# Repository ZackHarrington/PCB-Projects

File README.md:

# PCB Projects
This repository holds all my personal Autodesk Eagle (now Fusion 360 and KiCAD) projects and libraries

__Projects:__
- Billy Bass Board: 	A board to convert or 'hack' a Big Mouth Billy Bass into an IoT device - in progress
- Christmas Snow Globe:	A board using an ATtiny85 as a 6-hour timer IC in a custom snow globe - made as a gift
- Greek Keyboard:	A 5x6 key keyboard using an ATmega32u4 and HID to input Greek Unicode - made as a gift
- LED Test Board:	A simple board for testing any combination of LED, resistor, and power source
- USB UART Board:	Two small boards for programming ESP32 modules, each for a different USB-to-UART IC

__Libraries:__
- Aesthetics:	Silkscreen and copper designs
- Capacitors: 	SEM (Samsung Electro-Mechanics) MLCC capacitors
- Connectors: 	Board inputs or outputs
- Diodes:	Standard and Schottky diodes with Kingbright LEDs
- Energy:	Batteries and energy storage
- ICs: 		Integrates circuits
- Inductors:	SEM (Samsung Electro-Mechanics) Power Inductors
- Oscillators:	Crystal Oscillators
- Resistors:	SEM (Samsung Electro-Mechanics) CHIP-R chip resistors and potentiometers
- Switches: 	Physical buttons and switches
- Symbols:	Schematic symbols
- Transistors:	Discrete MOSFETs and BJTs

__Design Blocks:__
- ESP32 Wrover Module:	All standard capacitors and connections for implementing an ESP32-WROVER module

Note: I'm still in the process of finalizing the documentation for each project

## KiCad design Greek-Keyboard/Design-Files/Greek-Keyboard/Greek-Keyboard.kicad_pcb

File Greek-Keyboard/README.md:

# Greek Keyboard 

This project was built as a request from my brother. His desire was to have a separate keyboard he could use to input Greek letters while writing papers for school. This README goes through an overview of the features, build, and considerations for next time.

## Features

The following were the requested features for this project:
- A separate USB-C keyboard, with a similar look and feel to the Dell XPS-15 (his current laptop)
- Contain all the Greek letters in a small form factor
- If there is extra room add some other common characters (degree symbol, etc.)
- Make it not require Windows language switching

## Design

To meet all these requirements I first came up with a concept for a 5x6 key keyboard, which fit all the Greek letters on the first 4 rows. This left a 5th required row to fit the SHIFT key, and left room for some extra characters. For the extra characters we decided to add the degree symbol along with final sigma, and then add the most common Greek letter accents. For the keyboard keys I decided to go with Cherry MX keys since they were the most readily available and easy to use. The electronics for a keyboard is also relatively straightforward and well documented online. Thus, after some brief research I settled on a 5x6 key matrix to save pin space.  

For the keyboard firmware, and actually sending Windows a Greek character without language switching, I chose to use Unicode inputs. Unicode gives a unique code to every character in the majority of languages. To input a Unicode character you simply have to type in its hexadecimal sequence, followed by ALT + x. This indicates to Windows that the previous input is the hex code for a Unicode character and that they should be converted accordingly. To do this, I internally check for what combination of keys is pressed and then send the corresponding sequence and ALT + x in quick succession. I chose to implement all this through an Arduino Leonardo (ATmega32u4), so I only needed one USB connection for everything.

## Construction

Included below are some images of the final product.

### PCB

### Keyboard Backlights

## License

This is just a hobby creation I made as a gift so feel free to do whatever you want with this design if you happened upon it. However, I would recommend reading the considerations below and modifying it or building your own rather than copying it.

## Project Considerations

The following are some things I learned from this project for myself or anyone else to consider when doing something similar.
- Add an ICSP header and !RESET pin pullup - The ATmega32u4 does not come with a USB bootloader and you first have to program it in. This can be done in many different ways, but I chose to use an Arduino and the built in ArduinoISP.
- It would be easier to solder the Cherry keys in by printing the top of the enclosure first and using it to align them
- The keyboard sounds very different once in the enclosure, consider adding some foam or extra support from the enclosure to minimize the hollow clicking sound.

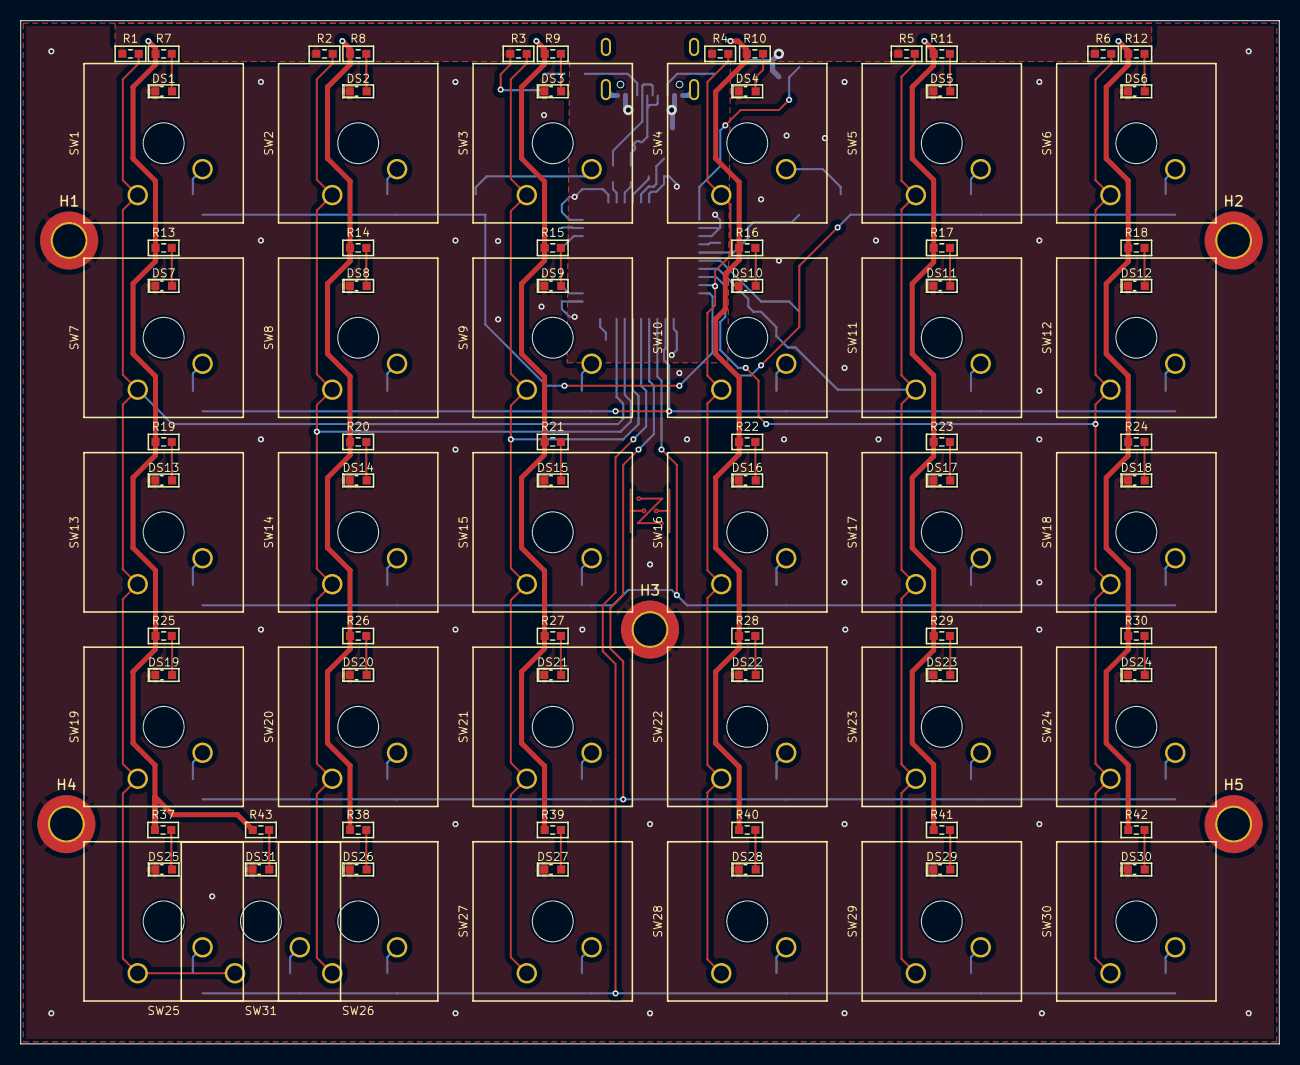
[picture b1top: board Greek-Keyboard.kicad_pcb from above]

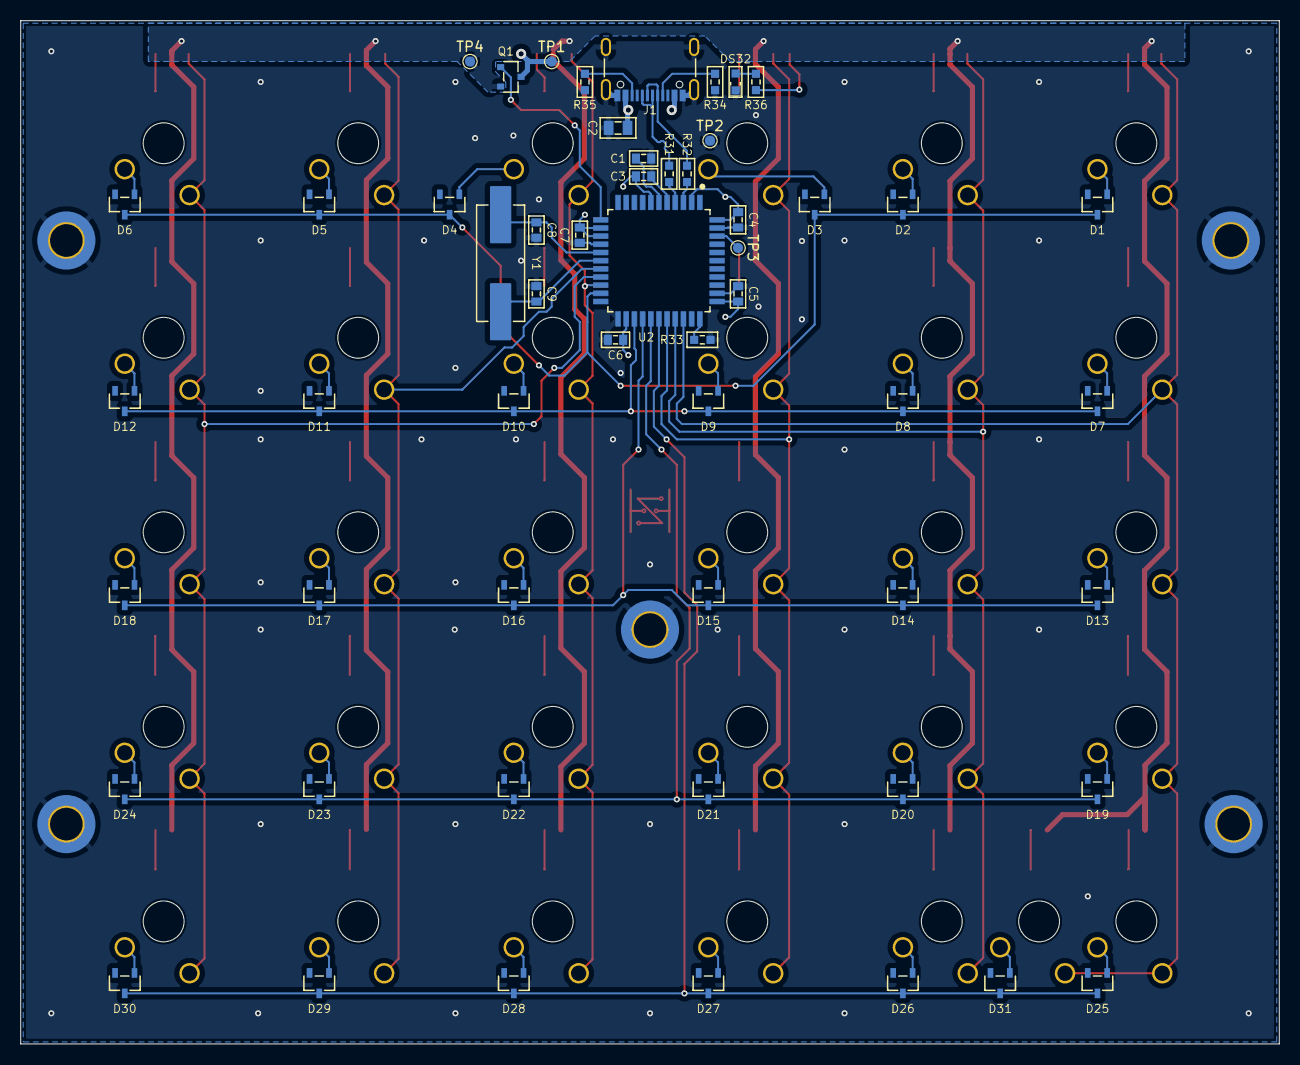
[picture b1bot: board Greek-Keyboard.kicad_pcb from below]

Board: 2 copper layers, 123.2 x 100.2 mm, 160 parts (55 on the bottom side), 89 nets.

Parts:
C1: 1uF±10%; 1608-SEM
C2: 10uF±10%; 2012-SEM
C3, C4, C5, C6, C7: 0.1uF±5%; 1608-SEM
C8, C9: 22pF±5%; 1608-SEM
D1, D2, D3, D4, D5, D6, D7, D8, D9, D10, D11, D12, D13, D14, D15, D16, D17, D18, D19, D20, D21, D22, D23, D24, D25, D26, D27, D28, D29, D30, D31: BAT54L; SOT-23-3
DS1, DS2, DS3, DS4, DS5, DS6, DS7, DS8, DS9, DS10, DS11, DS12, DS13, DS14, DS15, DS16, DS17, DS18, DS19, DS20, DS21, DS22, DS23, DS24, DS25, DS26, DS27, DS28, DS29, DS30, DS31: White; 1608
DS32: RED; 1608
H1, H2, H3, H4, H5: MountingHole_Pad; MountingHole_3.2mm_M3_ISO7380_Pad_TopBottom
J1: USB-C; USB-4105
Q1: BSS316N; SOT-23-3
R1, R2, R3, R4, R5, R6, R7, R8, R9, R10, R11, R12, R13, R14, R15, R16, R17, R18, R19, R20, R21, R22, R23, R24, R25, R26, R27, R28, R29, R30, R36, R37, R38, R39, R40, R41, R42, R43: 470Ω±1%; 1608-SEM
R31, R32: 22Ω±1%; 1608-SEM
R33: 10kΩ±1%; 1608-SEM
R34, R35: 5.1kΩ±1%; 1608-SEM
SW1, SW2, SW3, SW4, SW5, SW6, SW7, SW8, SW9, SW10, SW11, SW12, SW13, SW14, SW15, SW16, SW17, SW18, SW19, SW20, SW21, SW22, SW23, SW24, SW25, SW26, SW27, SW28, SW29, SW30, SW31: MX-Brown; MX-1-Pole
TP1, TP2, TP3, TP4: TestPoint; TestPoint_Pad_D1.0mm
U1: SIGNATURE
U2: ATmega32u4; TQFP44
Y1: 8MHz±25ppm; ABLS-ABRACON

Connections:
+5V: C2.1, C3.1, C4.1, C5.1, C6.1, C7.1, J1.A4_B9 (VBUS), J1.A9_B4 (VBUS), Q1.3, R1.1, R2.1, R3.1, R4.1, R5.1, R6.1, R36.1, TP1.1, U2.2 (UVcc), U2.7 (VBus), U2.13 (!RESET), U2.14 (VCC), U2.24 (AVCC), U2.34 (VCC), U2.44 (AVCC)
/Backlight LEDs/5V: Q1.2, R7.1, R8.1, R9.1, R10.1, R11.1, R12.1, R13.1, R14.1, R15.1, R16.1, R17.1, R18.1, R19.1, R20.1, R21.1, R22.1, R23.1, R24.1, R25.1, R26.1, R27.1, R28.1, R29.1, R30.1, R37.1, R38.1, R39.1, R40.1, R41.1, R42.1, R43.1, TP4.1
/D0: R4.2, SW4.2, SW10.2, SW16.2, SW22.2, SW28.2, U2.20 ((RXD1/INT2)_PD2)
/D1: D1.3, D2.3, D3.3, D4.3, D5.3, D6.3, U2.21 ((TXD1/INT3)_PD3)
/D2: R6.2, SW6.2, SW12.2, SW18.2, SW24.2, SW30.2, U2.19 ((SDA/INT1)_PD1)
/D3: R5.2, SW5.2, SW11.2, SW17.2, SW23.2, SW29.2, U2.18 ((SCL/INT0)_PD0)
/D4: D7.3, D8.3, D9.3, D10.3, D11.3, D12.3, U2.25 ((ICP1/ADC8)_PD4)
/D5: R1.2, SW1.2, SW7.2, SW13.2, SW19.2, SW25.2, SW31.2, U2.31 (PC6)
/D6: D19.3, D20.3, D21.3, D22.3, D23.3, D24.3, U2.27 ((T0/ADC10)_PD7)
/IO8: D25.3, D26.3, D27.3, D28.3, D29.3, D30.3, D31.3, U2.28 ((PCINT4/ADC11)_PB4)
/IO9: R3.2, SW3.2, SW9.2, SW15.2, SW21.2, SW27.2, U2.29 ((PCINT5/ADC12)_PB5)
/IO10: R2.2, SW2.2, SW8.2, SW14.2, SW20.2, SW26.2, U2.30 ((PCINT6/ADC13)_PB6)
/IO11: Q1.1, U2.12 ((PCINT7/!RTS)_PB7)
/IO12: D13.3, D14.3, D15.3, D16.3, D17.3, D18.3, U2.26 ((T1/ADC9)_PD6)
GND: C1.2, C2.2, C3.2, C4.2, C5.2, C6.2, C7.2, C8.1, C9.1, DS1.1, DS2.1, DS3.1, DS4.1, DS5.1, DS6.1, DS7.1, DS8.1, DS9.1, DS10.1, DS11.1, DS12.1, DS13.1, DS14.1, DS15.1, DS16.1, DS17.1, DS18.1, DS19.1, DS20.1, DS21.1, DS22.1, DS23.1, DS24.1, DS25.1, DS26.1, DS27.1, DS28.1, DS29.1, DS30.1, DS31.1, DS32.1, H1.1, H2.1, H3.1, H4.1, H5.1, J1.A1_B12 (GND), J1.A12_B1 (GND), J1.SHELL@1 (SHELL), J1.SHELL@2 (SHELL), J1.SHELL@3 (SHELL), J1.SHELL@4 (SHELL), R33.2, R34.2, R35.2, TP2.1, U2.5 (UGnd), U2.15 (GND), U2.23 (GND), U2.35 (GND), U2.43 (GND)
unnamed: D1.1, SW1.1
unnamed: D2.1, SW2.1
unnamed: D3.1, SW3.1
unnamed: D4.1, SW4.1
unnamed: D5.1, SW5.1
unnamed: D6.1, SW6.1
unnamed: D7.1, SW7.1
unnamed: D8.1, SW8.1
unnamed: D9.1, SW9.1
unnamed: D10.1, SW10.1
unnamed: D11.1, SW11.1
unnamed: D12.1, SW12.1
unnamed: D13.1, SW13.1
unnamed: D14.1, SW14.1
unnamed: D15.1, SW15.1
unnamed: D16.1, SW16.1
unnamed: D17.1, SW17.1
unnamed: D18.1, SW18.1
unnamed: D19.1, SW19.1
unnamed: D20.1, SW20.1
unnamed: D21.1, SW21.1
unnamed: D22.1, SW22.1
unnamed: D23.1, SW23.1
unnamed: D24.1, SW24.1
unnamed: D25.1, SW25.1
unnamed: D26.1, SW26.1
unnamed: D27.1, SW27.1
unnamed: D28.1, SW28.1
unnamed: D29.1, SW29.1
unnamed: D30.1, SW30.1
unnamed: D31.1, SW31.1
unnamed: DS1.2, R7.2
unnamed: DS2.2, R8.2
unnamed: DS3.2, R9.2
unnamed: DS4.2, R10.2
unnamed: DS5.2, R11.2
unnamed: DS6.2, R12.2
unnamed: DS7.2, R13.2
unnamed: DS8.2, R14.2
unnamed: DS9.2, R15.2
unnamed: DS10.2, R16.2
unnamed: DS11.2, R17.2
unnamed: DS12.2, R18.2
unnamed: DS13.2, R19.2
unnamed: DS14.2, R20.2
unnamed: DS15.2, R21.2
unnamed: DS16.2, R22.2
unnamed: DS17.2, R23.2
unnamed: DS18.2, R24.2
unnamed: DS19.2, R25.2
unnamed: DS20.2, R26.2
unnamed: DS21.2, R27.2
unnamed: DS22.2, R28.2
unnamed: DS23.2, R29.2
unnamed: DS24.2, R30.2
unnamed: DS25.2, R37.2
unnamed: DS26.2, R38.2
unnamed: DS27.2, R39.2
unnamed: DS28.2, R40.2
unnamed: DS29.2, R41.2
unnamed: DS30.2, R42.2
unnamed: DS31.2, R43.2
unnamed: DS32.2, R36.2
unnamed: J1.A5 (CC1), R34.1
unnamed: J1.B5 (CC2), R35.1
unnamed: J1.A7 (DN1), J1.B7 (DN2), R32.1
unnamed: J1.A6 (DP1), J1.B6 (DP2), R31.1
unnamed: R33.1, U2.33 ((!HWB)_PE2)
unnamed: TP3.1, U2.42 (AREF)
unnamed: R31.2, U2.4 (D+)
unnamed: R32.2, U2.3 (D-)
unnamed: C1.1, U2.6 (UCap)
unnamed: C9.2, U2.17 (XTAL1), Y1.2
unnamed: C8.2, U2.16 (XTAL2), Y1.1

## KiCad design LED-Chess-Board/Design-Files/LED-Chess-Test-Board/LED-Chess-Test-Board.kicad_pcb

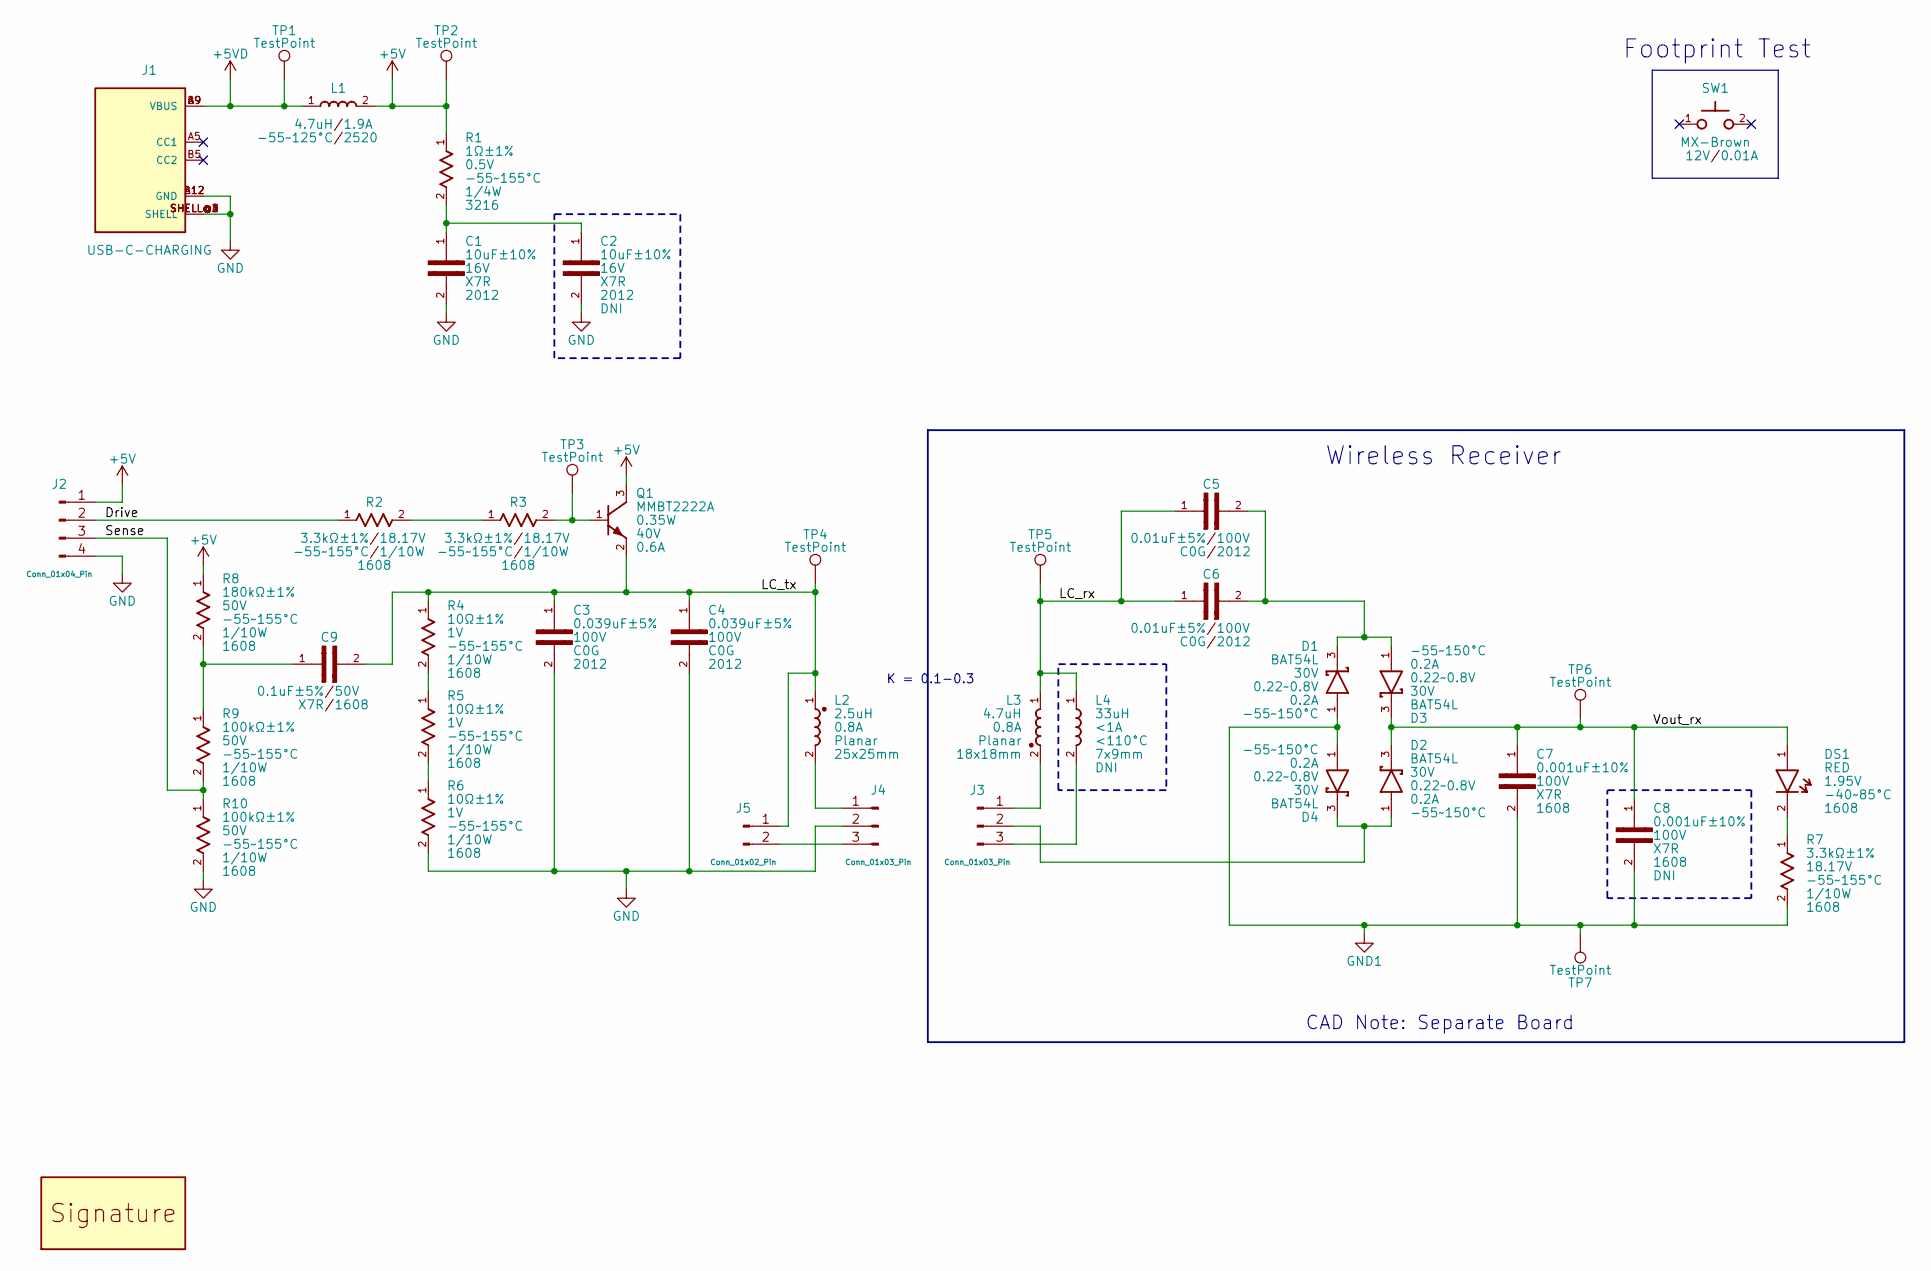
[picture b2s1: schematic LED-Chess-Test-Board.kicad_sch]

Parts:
C1, C2: 10uF±10%; 2012-SEM; VOLTAGE 16V
C3, C4: 0.039uF±5%; 2012-SEM; VOLTAGE 100V
C5, C6: 0.01uF±5%; 2012-SEM; VOLTAGE 100V
C7, C8: 0.001uF±10%; 1608-SEM; VOLTAGE 100V
C9: 0.1uF±5%; 1608-SEM; VOLTAGE 50V
D1, D2, D3, D4: BAT54L; SOT-23-3
DS1: RED; 1608; VOLTAGE 1.95V
J1: USB-C-CHARGING; USB-4125
J2: Conn_01x04_Pin; PinHeader_1x04_P2.54mm_Vertical
J3, J4: Conn_01x03_Pin; PinHeader_1x03_P2.54mm_Vertical
J5: Conn_01x02_Pin; PinHeader_1x02_P2.54mm_Vertical
L1: 4.7uH; 2520-SEM
L2: 2.5uH; PLANAR-2.5uH-25x25mm
L3: 4.7uH; PLANAR-4.7uH-18x18mm
L4: 33uH; 7x9mm-TH
Q1: MMBT2222A; SOT-23-3
R1: 1Ω±1%; 3216-SEM; VOLTAGE 0.5V
R2, R3, R7: 3.3kΩ±1%; 1608-SEM; VOLTAGE 18.17V
R4, R5, R6: 10Ω±1%; 1608-SEM; VOLTAGE 1V
R8: 180kΩ±1%; 1608-SEM; VOLTAGE 50V
R9, R10: 100kΩ±1%; 1608-SEM; VOLTAGE 50V
SW1: MX-Brown; MX-1-Pole
TP1, TP2, TP3, TP4, TP5, TP6, TP7: TestPoint; TestPoint_Pad_D1.0mm
U1: SIGNATURE

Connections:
+5V: J2.1, L1.2, Q1.3, R1.1, R8.1, TP2.1
+5VD: J1.A9 (VBUS), J1.B9 (VBUS), L1.1, TP1.1
/Drive: J2.2, R2.1
/LC_rx: C5.1, C6.1, L3.1, L4.1, TP5.1
/LC_tx: C3.1, C4.1, C9.2, J5.1, L2.1, Q1.2, R4.1, TP4.1
/Sense: J2.3, R9.2, R10.1
/Vout_rx: C7.1, C8.1, D2.3, D3.3, DS1.1, TP6.1
GND: C1.2, C2.2, C3.2, C4.2, J1.A12 (GND), J1.B12 (GND), J1.SHELL@1 (SHELL), J1.SHELL@2 (SHELL), J1.SHELL@3 (SHELL), J1.SHELL@4 (SHELL), J2.4, J4.2, R6.2, R10.2
GND1: C7.2, C8.2, D1.1, D4.1, R7.2, TP7.1
unnamed: C1.1, C2.1, R1.2
unnamed: C5.2, C6.2, D1.3, D3.1
unnamed: C9.1, R8.2, R9.1
unnamed: DS1.2, R7.1
unnamed: J3.1, L3.2
unnamed: D2.1, D4.3, J3.2
unnamed: J3.3, L4.2
unnamed: J4.1, L2.2
unnamed: J4.3, J5.2
unnamed: Q1.1, R3.2, TP3.1
unnamed: R2.2, R3.1
unnamed: R4.2, R5.1
unnamed: R5.2, R6.1

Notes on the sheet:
Footprint Test
K = 0.1-0.3
CAD Note: Separate Board
Wireless Receiver

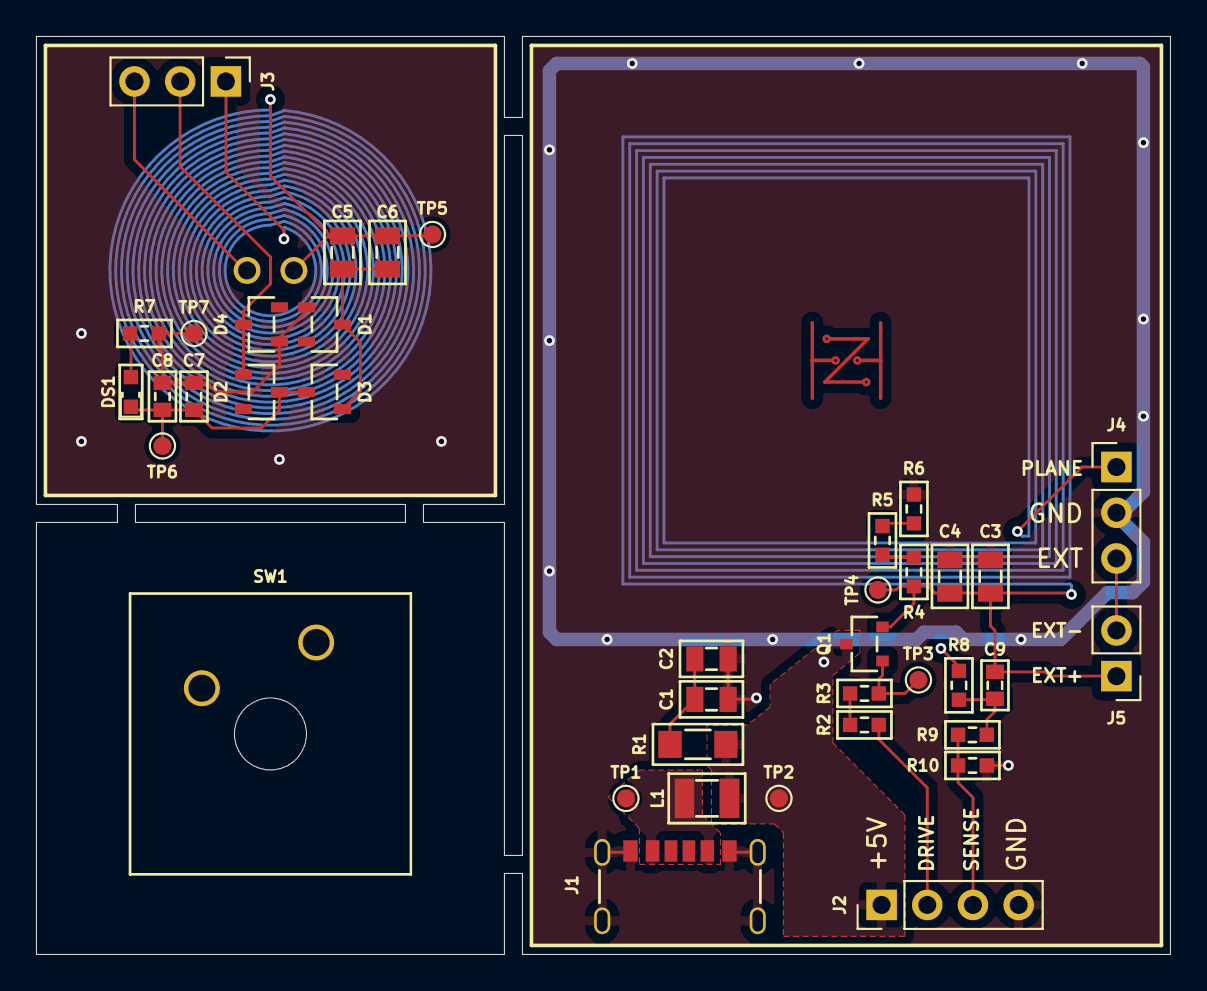
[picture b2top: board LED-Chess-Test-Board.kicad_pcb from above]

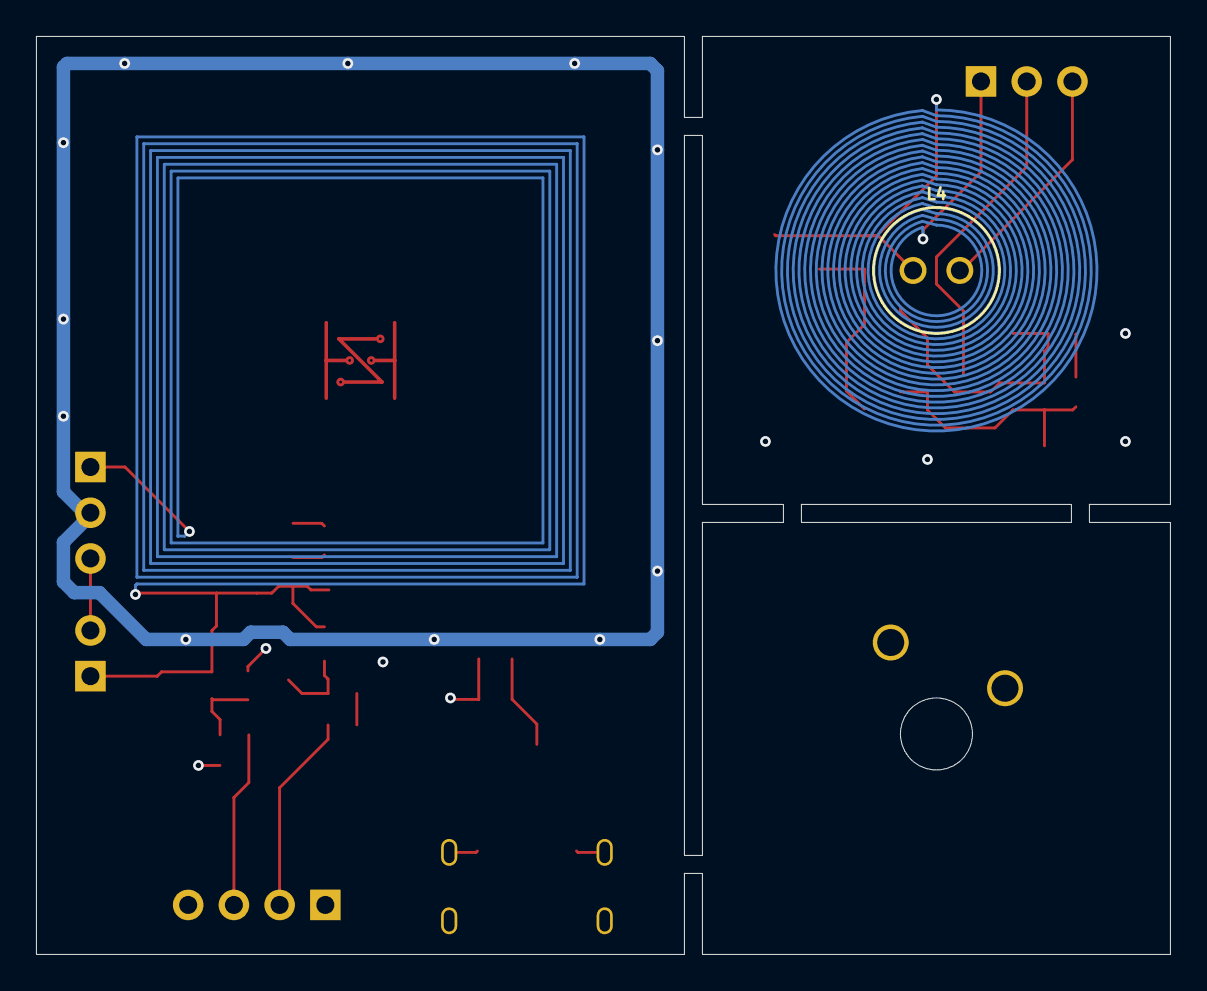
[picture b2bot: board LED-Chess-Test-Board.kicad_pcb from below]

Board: 4 copper layers, 63.0 x 51.0 mm, 43 parts (3 on the bottom side), 22 nets.

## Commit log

2023-04-29 Initial commit with gitignore and README files
2023-04-29 Adding all current project files and libraries
2023-06-04 Updated gitignore for gerber files
2023-06-04 Finished Billy Bass Board V2.0.0
2023-06-10 Updated files to match parts purchased
2024-01-08 Updated gitignore for next large commit
2024-01-09 Few new projects. Migration of all updated projects and libraries to Fusion 360 Elecronics
2024-01-10 Attempted to create a Christmas Snow Globe README
2024-01-10 Adjusted links in Christmas Snow Globe README
2024-01-10 Adjusted links again in Christmas Snow Globe README
2024-01-10 Adjusted links another time in Christmas Snow Globe README
2024-02-18 Added 2 month update
2024-03-21 Updated .gitingnore
2024-03-21 Billy Bass Board v3.0.0 Update
2024-03-22 Updated Billy-Bass-Board README
2024-03-22 Updated Billy-Bass-Board README grammar
2024-10-13 Edited .gitignore for migration to KiCAD
2024-10-13 Migrated libraries to KiCAD and started testing a new chess board project
2024-12-28 Added Greek Keyboard Project
2024-12-28 Adjusted photos
